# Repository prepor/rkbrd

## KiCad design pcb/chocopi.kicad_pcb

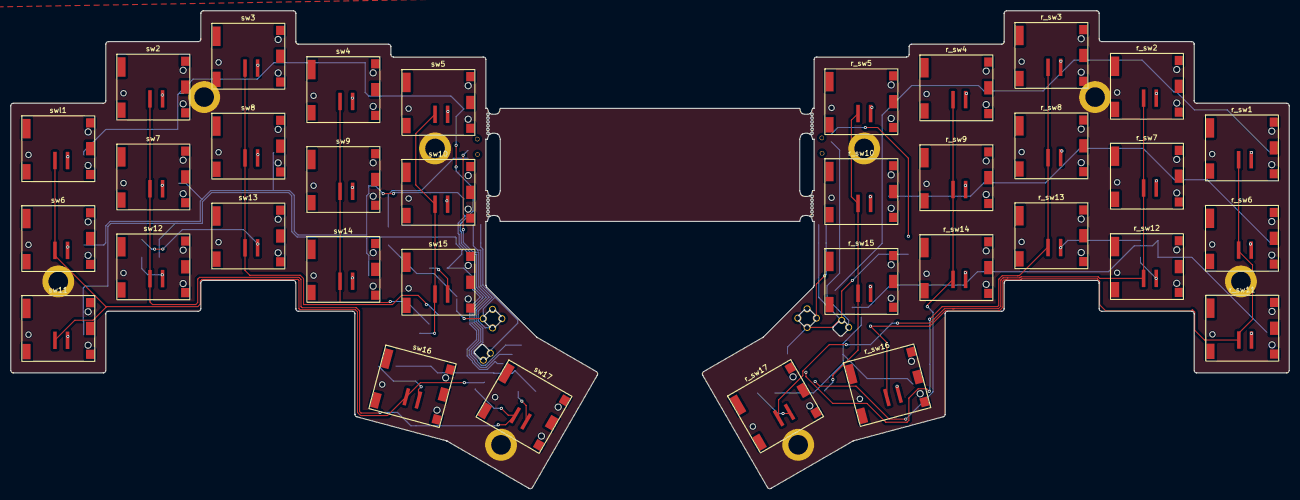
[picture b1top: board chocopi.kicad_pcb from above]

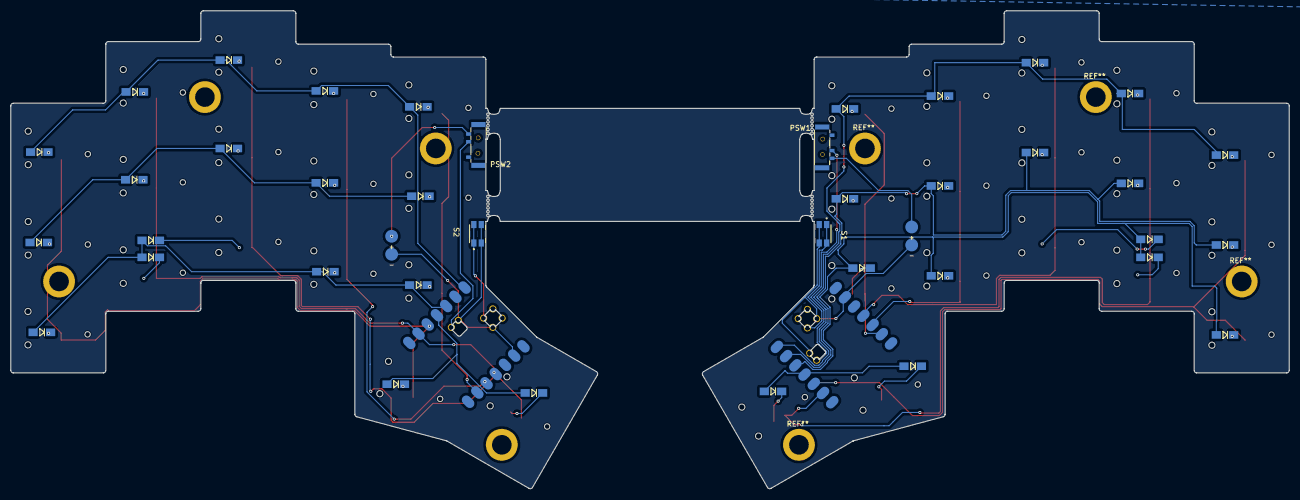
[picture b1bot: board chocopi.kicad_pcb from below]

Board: 2 copper layers, 248.9 x 93.1 mm, 78 parts (44 on the bottom side), 60 nets.

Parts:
BAT+1, BAT+2: +; BatteryPad
BATGND1, BATGND2: -; BatteryPad
D1, D2, D3, D4, D5, D6, D7, D8, D9, D10, D11, D12, D13, D14, D15, D16, D17: Diode_SOD123
PSW1, PSW2: SW_SPDT; MSK12C02
S1, S2: EVQ-P7A01P; SW_EVQ-P7A01P
U1, U2: XIAO-nRF52840-SMD; xiao-ble-smd-cutout
r_D1, r_D2, r_D3, r_D4, r_D5, r_D6, r_D7, r_D8, r_D9, r_D10, r_D11, r_D12, r_D13, r_D14, r_D15, r_D16, r_D17: Diode_SOD123
r_sw1, r_sw2, r_sw3, r_sw4, r_sw5, r_sw6, r_sw7, r_sw8, r_sw9, r_sw10, r_sw11, r_sw12, r_sw13, r_sw14, r_sw15, r_sw16, r_sw17: Cherry_ULP_SMD
sw2, sw3, sw4, sw5, sw6, sw7, sw8, sw9, sw10, sw11, sw12, sw13, sw14, sw15, sw16, sw17: Cherry_ULP_SMD
swl1: Cherry_ULP_SMD

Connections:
unnamed: D1.1 (K), swl1.2
unnamed: D2.1 (K), sw2.2
unnamed: D3.1 (K), sw3.2
unnamed: D4.1 (K), sw4.2
unnamed: D5.1 (K), sw5.2
unnamed: D6.1 (K), sw6.2
unnamed: D7.1 (K), sw7.2
unnamed: D8.1 (K), sw8.2
unnamed: D9.1 (K), sw9.2
unnamed: D10.1 (K), sw10.2
unnamed: D11.1 (K), sw11.2
unnamed: D12.1 (K), sw12.2
unnamed: D13.1 (K), sw13.2
unnamed: D14.1 (K), sw14.2
unnamed: D15.1 (K), sw15.2
unnamed: D16.1 (K), sw16.2
unnamed: D17.1 (K), sw17.2
unnamed: r_D1.1 (K), r_sw1.2
unnamed: r_D2.1 (K), r_sw2.2
unnamed: r_D3.1 (K), r_sw3.2
unnamed: r_D4.1 (K), r_sw4.2
unnamed: r_D5.1 (K), r_sw5.2
unnamed: r_D6.1 (K), r_sw6.2
unnamed: r_D7.1 (K), r_sw7.2
unnamed: r_D8.1 (K), r_sw8.2
unnamed: r_D9.1 (K), r_sw9.2
unnamed: r_D10.1 (K), r_sw10.2
unnamed: r_D11.1 (K), r_sw11.2
unnamed: r_D12.1 (K), r_sw12.2
unnamed: r_D13.1 (K), r_sw13.2
unnamed: r_D14.1 (K), r_sw14.2
unnamed: r_D15.1 (K), r_sw15.2
unnamed: r_D16.1 (K), r_sw16.2
unnamed: r_D17.1 (K), r_sw17.2
l_BAT+: PSW1.2 (B), U1.19 (BAT)
l_GND: BATGND1.1, S1.2_1, S1.2_2, U1.13 (GND), U1.18 (GND), U1.20 (GND)
l_RESET: S1.1_1, S1.1_2, U1.17 (RESET)
l_VBAT: BAT+1.1, PSW1.3 (C)
l_col1: U1.5 (A8_SDA/0.04_H), sw6.1, sw11.1, sw16.1, swl1.1
l_col2: U1.6 (A9_SCL/0.05_H), sw2.1, sw7.1, sw12.1, sw17.1
l_col3: U1.11 (A6_MOSI/1.15), sw3.1, sw8.1, sw13.1
l_col4: U1.10 (A5_MISO/1.14), sw4.1, sw9.1, sw14.1
l_col5: U1.9 (A7_SCK/1.13), sw5.1, sw10.1, sw15.1
l_row1: D1.2 (A), D2.2 (A), D3.2 (A), D4.2 (A), D5.2 (A), U1.1 (A2/0.02_H)
l_row2: D6.2 (A), D7.2 (A), D8.2 (A), D9.2 (A), D10.2 (A), U1.2 (A4/0.03_H)
l_row3: D11.2 (A), D12.2 (A), D13.2 (A), D14.2 (A), D15.2 (A), U1.3 (A10/0.28)
l_row4: D16.2 (A), D17.2 (A), U1.4 (A11/0.29)
r_BAT+: PSW2.2 (B), U2.19 (BAT)
r_GND: BATGND2.1, S2.2_1, S2.2_2, U2.13 (GND), U2.18 (GND), U2.20 (GND)
r_RESET: S2.1_1, S2.1_2, U2.17 (RESET)
r_VBAT: BAT+2.1, PSW2.3 (C)
r_col1: U2.5 (A8_SDA/0.04_H), r_sw1.1, r_sw6.1, r_sw11.1, r_sw16.1
r_col2: U2.6 (A9_SCL/0.05_H), r_sw2.1, r_sw7.1, r_sw12.1, r_sw17.1
r_col3: U2.11 (A6_MOSI/1.15), r_sw3.1, r_sw8.1, r_sw13.1
r_col4: U2.10 (A5_MISO/1.14), r_sw4.1, r_sw9.1, r_sw14.1
r_col5: U2.9 (A7_SCK/1.13), r_sw5.1, r_sw10.1, r_sw15.1
r_row1: U2.1 (A2/0.02_H), r_D1.2 (A), r_D2.2 (A), r_D3.2 (A), r_D4.2 (A), r_D5.2 (A)
r_row2: r_D6.2 (A), r_D7.2 (A), r_D8.2 (A), r_D9.2 (A), r_D10.2 (A)
r_row3: U2.3 (A10/0.28), r_D11.2 (A), r_D12.2 (A), r_D13.2 (A), r_D14.2 (A), r_D15.2 (A)
r_row4: U2.4 (A11/0.29), r_D16.2 (A), r_D17.2 (A)

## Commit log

2025-04-19 init
2025-04-19 fix diode
2025-04-20 positioned
2025-04-21 mousebites!
2025-05-16 moving
2025-06-03 2 wip
2025-06-05 rkbrd3 init
2025-06-05 typo
